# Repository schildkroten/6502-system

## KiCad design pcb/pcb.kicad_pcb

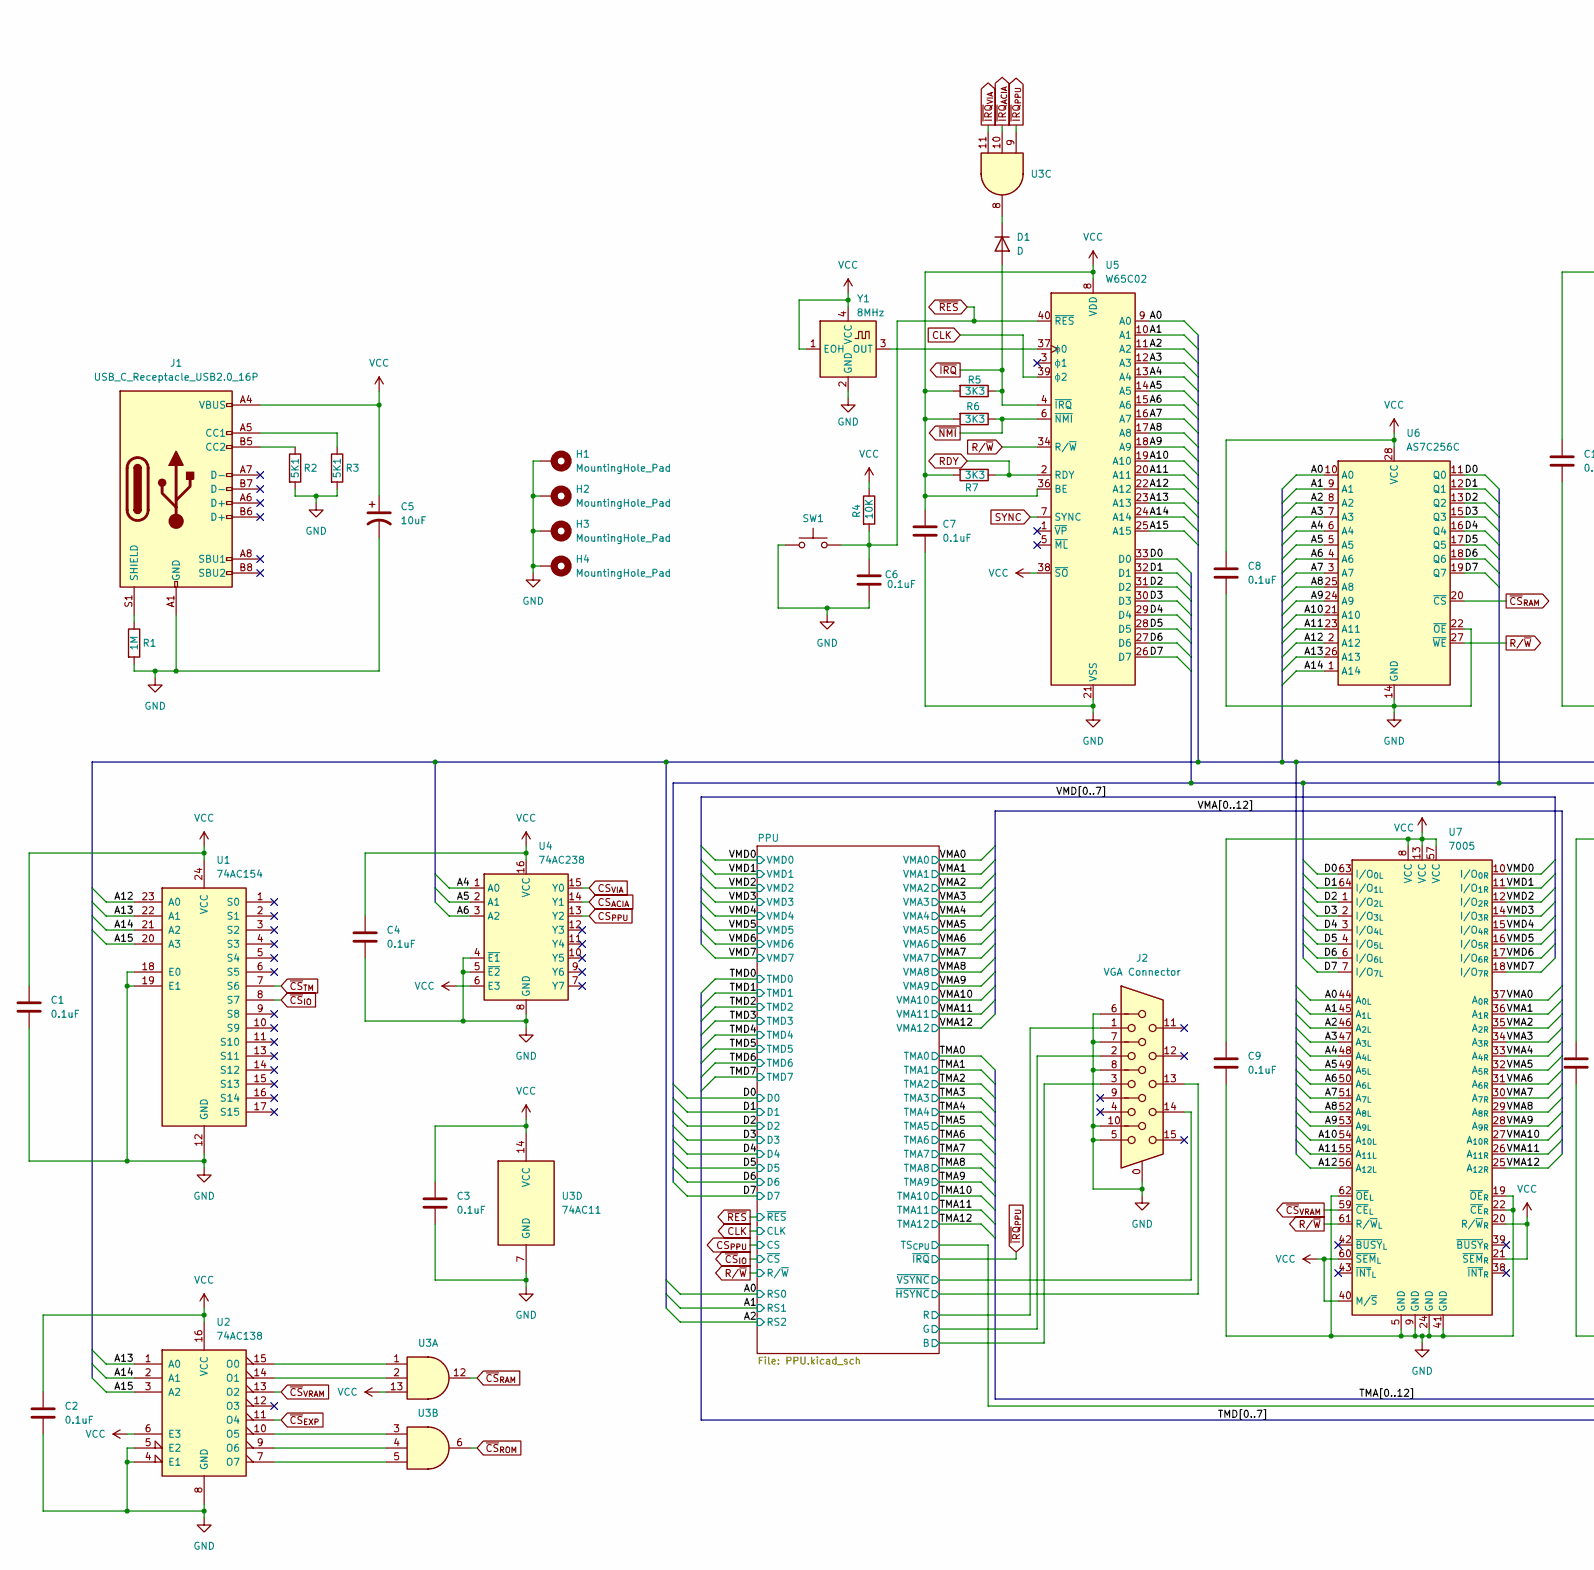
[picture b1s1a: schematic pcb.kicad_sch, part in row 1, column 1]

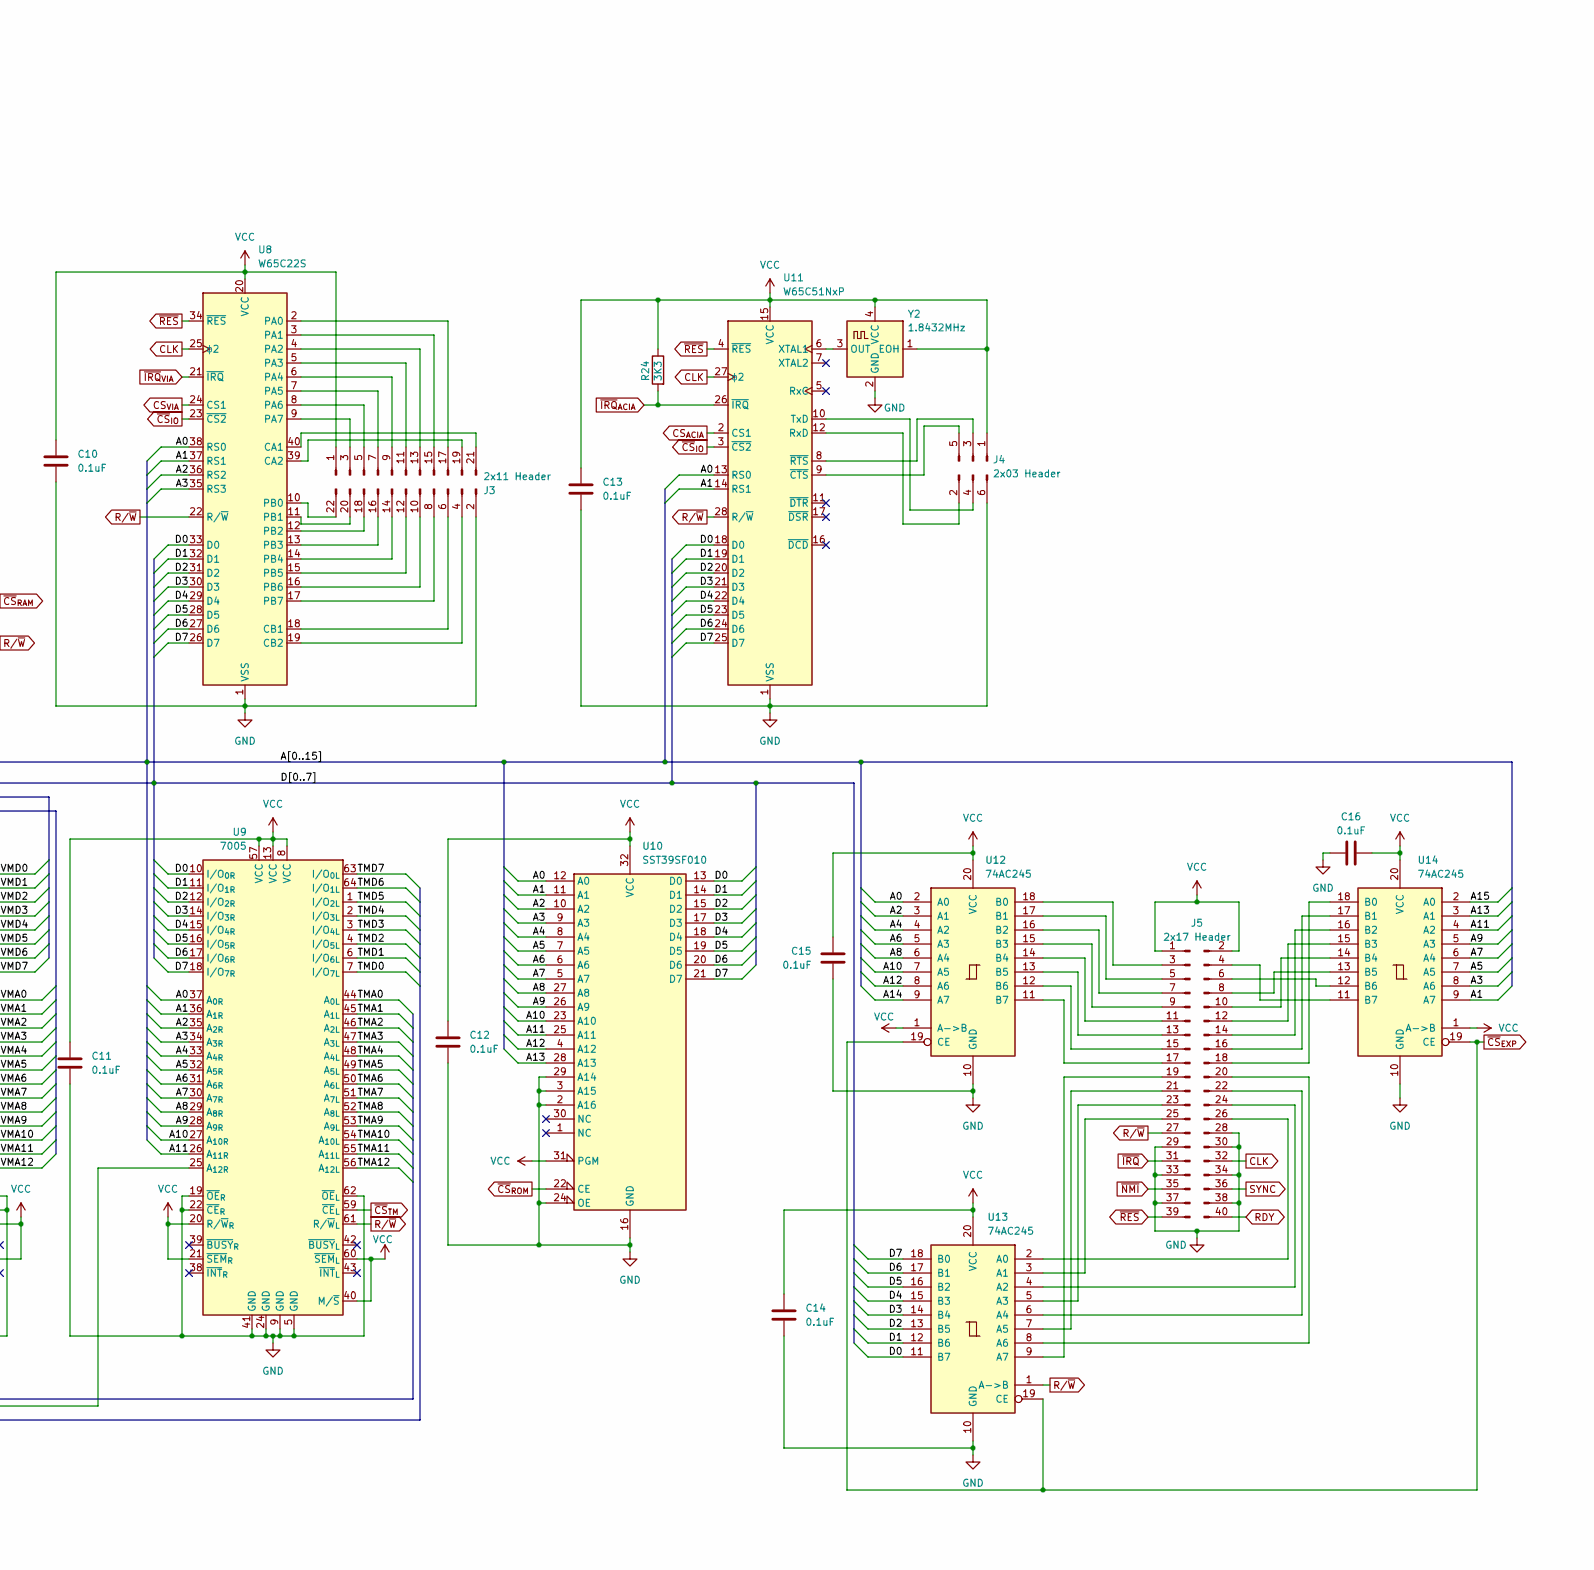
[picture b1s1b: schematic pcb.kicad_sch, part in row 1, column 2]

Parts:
C1, C2, C3, C4, C6, C7, C8, C9, C10, C11, C12, C13, C14, C15, C16: 0.1uF; C_0805_2012Metric
C5: 10uF; C_Radial_D5.0mm_H7.0mm_P2.00mm
D1: D
H1, H2, H3, H4: MountingHole_Pad; MountingHole_3.2mm_M3_Pad
J1: USB_C_Receptacle_USB2.0_16P; USB_C_Receptacle_GCT_USB4085
J2: VGA Connector; DSUB-15-HD_Socket_Horizontal_P2.29x2.54mm_EdgePinOffset8.35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
J3: 2x11 Header; IDC-Header_2x11_P2.54mm_Horizontal
J4: 2x03 Header; IDC-Header_2x03_P2.54mm_Horizontal
J5: 2x17 Header; IDC-Header_2x20_P2.54mm_Horizontal
R1: 1M; R_0805_2012Metric
R2, R3: 5K1; R_0805_2012Metric
R4: 10K; R_0805_2012Metric
R5, R6, R7, R24: 3K3; R_0805_2012Metric
SW1: SW_Push; SW_PUSH_6mm
U1: 74AC154; SOIC-24W_7.5x15.4mm_P1.27mm
U2: 74AC138; SOIC-16_3.9x9.9mm_P1.27mm
U3: 74AC11; SOIC-14_3.9x8.7mm_P1.27mm
U4: 74AC238; SOIC-16_3.9x9.9mm_P1.27mm
U5: W65C02; DIP-40_W15.24mm_Socket
U6: AS7C256C; DIP-28_W7.62mm_Socket
U7, U9: 7005; TQFP-64_14x14mm_P0.8mm
U8: W65C22S; DIP-40_W15.24mm_Socket
U10: SST39SF010; PLCC-32_THT-Socket
U11: W65C51NxP; DIP-28_W15.24mm_Socket
U12, U13, U14: 74AC245; TSSOP-20_4.4x6.5mm_P0.65mm
Y1: 8MHz; Oscillator_SMD_SeikoEpson_SG8002CA-4Pin_7.0x5.0mm
Y2: 1.8432MHz; Oscillator_SMD_SeikoEpson_SG8002CA-4Pin_7.0x5.0mm

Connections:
/A0: U5.9 (A0), U6.10 (A0), U7.44 (A_{0L}), U8.38 (RS0), U9.37 (A_{0R}), U10.12 (A0), U11.13 (RS0), U12.2 (A0); also elsewhere on the board
/A1: U5.10 (A1), U6.9 (A1), U7.45 (A_{1L}), U8.37 (RS1), U9.36 (A_{1R}), U10.11 (A1), U11.14 (RS1), U14.9 (A7); also elsewhere on the board
/A2: U5.11 (A2), U6.8 (A2), U7.46 (A_{2L}), U8.36 (RS2), U9.35 (A_{2R}), U10.10 (A2), U12.3 (A1); also elsewhere on the board
/A3: U5.12 (A3), U6.7 (A3), U7.47 (A_{3L}), U8.35 (RS3), U9.34 (A_{3R}), U10.9 (A3), U14.8 (A6)
/A4: U4.1 (A0), U5.13 (A4), U6.6 (A4), U7.48 (A_{4L}), U9.33 (A_{4R}), U10.8 (A4), U12.4 (A2)
/A5: U4.2 (A1), U5.14 (A5), U6.5 (A5), U7.49 (A_{5L}), U9.32 (A_{5R}), U10.7 (A5), U14.7 (A5)
/A6: U4.3 (A2), U5.15 (A6), U6.4 (A6), U7.50 (A_{6L}), U9.31 (A_{6R}), U10.6 (A6), U12.5 (A3)
/A7: U5.16 (A7), U6.3 (A7), U7.51 (A_{7L}), U9.30 (A_{7R}), U10.5 (A7), U14.6 (A4)
/A8: U5.17 (A8), U6.25 (A8), U7.52 (A_{8L}), U9.29 (A_{8R}), U10.27 (A8), U12.6 (A4)
/A9: U5.18 (A9), U6.24 (A9), U7.53 (A_{9L}), U9.28 (A_{9R}), U10.26 (A9), U14.5 (A3)
/A10: U5.19 (A10), U6.21 (A10), U7.54 (A_{10L}), U9.27 (A_{10R}), U10.23 (A10), U12.7 (A5)
/A11: U5.20 (A11), U6.23 (A11), U7.55 (A_{11L}), U9.26 (A_{11R}), U10.25 (A11), U14.4 (A2)
/A12: U1.23 (A0), U5.22 (A12), U6.2 (A12), U7.56 (A_{12L}), U10.4 (A12), U12.8 (A6)
/A13: U1.22 (A1), U2.1 (A0), U5.23 (A13), U6.26 (A13), U10.28 (A13), U14.3 (A1)
/A14: U1.21 (A2), U2.2 (A1), U5.24 (A14), U6.1 (A14), U12.9 (A7)
/A15: U1.20 (A3), U2.3 (A2), U5.25 (A15), U14.2 (A0)
/D0: U5.33 (D0), U6.11 (Q0), U7.63 (I/O_{0L}), U8.33 (D0), U9.10 (I/O_{0R}), U10.13 (D0), U11.18 (D0), U13.11 (B7); also elsewhere on the board
/D1: U5.32 (D1), U6.12 (Q1), U7.64 (I/O_{1L}), U8.32 (D1), U9.11 (I/O_{1R}), U10.14 (D1), U11.19 (D1), U13.12 (B6); also elsewhere on the board
/D2: U5.31 (D2), U6.13 (Q2), U7.1 (I/O_{2L}), U8.31 (D2), U9.12 (I/O_{2R}), U10.15 (D2), U11.20 (D2), U13.13 (B5); also elsewhere on the board
/D3: U5.30 (D3), U6.15 (Q3), U7.2 (I/O_{3L}), U8.30 (D3), U9.14 (I/O_{3R}), U10.17 (D3), U11.21 (D3), U13.14 (B4); also elsewhere on the board
/D4: U5.29 (D4), U6.16 (Q4), U7.3 (I/O_{4L}), U8.29 (D4), U9.15 (I/O_{4R}), U10.18 (D4), U11.22 (D4), U13.15 (B3); also elsewhere on the board
/D5: U5.28 (D5), U6.17 (Q5), U7.4 (I/O_{5L}), U8.28 (D5), U9.16 (I/O_{5R}), U10.19 (D5), U11.23 (D5), U13.16 (B2); also elsewhere on the board
/D6: U5.27 (D6), U6.18 (Q6), U7.6 (I/O_{6L}), U8.27 (D6), U9.17 (I/O_{6R}), U10.20 (D6), U11.24 (D6), U13.17 (B1); also elsewhere on the board
/D7: U5.26 (D7), U6.19 (Q7), U7.7 (I/O_{7L}), U8.26 (D7), U9.18 (I/O_{7R}), U10.21 (D7), U11.25 (D7), U13.18 (B0); also elsewhere on the board
/PPU/B: J2.3; also elsewhere on the board
/PPU/G: J2.2; also elsewhere on the board
/PPU/R: J2.1; also elsewhere on the board
/PPU/TS_{CPU}: U9.25 (A_{12R}); also elsewhere on the board
/PPU/~HSYNC: J2.13; also elsewhere on the board
/PPU/~VSYNC: J2.14; also elsewhere on the board
/TMA0: U9.44 (A_{0L}); also elsewhere on the board
/TMA1: U9.45 (A_{1L}); also elsewhere on the board
/TMA2: U9.46 (A_{2L}); also elsewhere on the board
/TMA3: U9.47 (A_{3L}); also elsewhere on the board
/TMA4: U9.48 (A_{4L}); also elsewhere on the board
/TMA5: U9.49 (A_{5L}); also elsewhere on the board
/TMA6: U9.50 (A_{6L}); also elsewhere on the board
/TMA7: U9.51 (A_{7L}); also elsewhere on the board
/TMA8: U9.52 (A_{8L}); also elsewhere on the board
/TMA9: U9.53 (A_{9L}); also elsewhere on the board
/TMA10: U9.54 (A_{10L}); also elsewhere on the board
/TMA11: U9.55 (A_{11L}); also elsewhere on the board
/TMA12: U9.56 (A_{12L}); also elsewhere on the board
/TMD0: U9.7 (I/O_{7L}); also elsewhere on the board
/TMD1: U9.6 (I/O_{6L}); also elsewhere on the board
/TMD2: U9.4 (I/O_{5L}); also elsewhere on the board
/TMD3: U9.3 (I/O_{4L}); also elsewhere on the board
/TMD4: U9.2 (I/O_{3L}); also elsewhere on the board
/TMD5: U9.1 (I/O_{2L}); also elsewhere on the board
/TMD6: U9.64 (I/O_{1L}); also elsewhere on the board
/TMD7: U9.63 (I/O_{0L}); also elsewhere on the board
/VMA0: U7.37 (A_{0R}); also elsewhere on the board
/VMA1: U7.36 (A_{1R}); also elsewhere on the board
/VMA2: U7.35 (A_{2R}); also elsewhere on the board
/VMA3: U7.34 (A_{3R}); also elsewhere on the board
/VMA4: U7.33 (A_{4R}); also elsewhere on the board
/VMA5: U7.32 (A_{5R}); also elsewhere on the board
/VMA6: U7.31 (A_{6R}); also elsewhere on the board
/VMA7: U7.30 (A_{7R}); also elsewhere on the board
/VMA8: U7.29 (A_{8R}); also elsewhere on the board
/VMA9: U7.28 (A_{9R}); also elsewhere on the board
/VMA10: U7.27 (A_{10R}); also elsewhere on the board
/VMA11: U7.26 (A_{11R}); also elsewhere on the board
/VMA12: U7.25 (A_{12R}); also elsewhere on the board
/VMD0: U7.10 (I/O_{0R}); also elsewhere on the board
/VMD1: U7.11 (I/O_{1R}); also elsewhere on the board
/VMD2: U7.12 (I/O_{2R}); also elsewhere on the board
/VMD3: U7.14 (I/O_{3R}); also elsewhere on the board
/VMD4: U7.15 (I/O_{4R}); also elsewhere on the board
/VMD5: U7.16 (I/O_{5R}); also elsewhere on the board
/VMD6: U7.17 (I/O_{6R}); also elsewhere on the board
/VMD7: U7.18 (I/O_{7R}); also elsewhere on the board
CLK: J5.32, U5.39 (ϕ2), U8.25 (ϕ2), U11.27 (ϕ2); also elsewhere on the board
CS_{ACIA}: U4.14 (Y1), U11.2 (CS1)
CS_{PPU}: U4.13 (Y2); also elsewhere on the board
CS_{VIA}: U4.15 (Y0), U8.24 (CS1)
GND: C1.2, C2.2, C3.2, C4.2, C5.2, C6.1, C7.2, C8.2, C9.2, C10.2, C11.2, C12.2, C13.2, C14.2, C15.2, C16.1, H1.1, H2.1, H3.1, H4.1, J1.A1 (GND), J1.A12 (GND), J1.B1 (GND), J1.B12 (GND), J2.0, J2.5, J2.6, J2.7, J2.8, J2.10, J3.2, J4.6, J5.28, J5.29, J5.30, J5.33, J5.34, J5.37, J5.38, R1.2, R2.2, R3.2, SW1.1, U1.12 (GND), U1.18 (E0), U1.19 (E1), U2.4 (E1), U2.5 (E2), U2.8 (GND), U3.7 (GND), U4.4 (~E1), U4.5 (~E2), U4.8 (GND), U5.21 (VSS), U6.14 (GND), U6.22 (~OE), U7.5 (GND), U7.9 (GND), U7.19 (~OE_{R}), U7.22 (~CE_{R}), U7.24 (GND), U7.41 (GND), U7.62 (~OE_{L}), U8.1 (VSS), U9.5 (GND), U9.9 (GND), U9.19 (~OE_{R}), U9.22 (~CE_{R}), U9.24 (GND), U9.41 (GND), U9.62 (~OE_{L}), U10.2 (A16), U10.3 (A15), U10.16 (GND), U10.24 (OE), U10.29 (A14), U11.1 (VSS), U12.10 (GND), U13.10 (GND), U14.10 (GND), Y1.2 (GND), Y2.2 (GND); also elsewhere on the board
unnamed: D1.1 (K), U3.8
unnamed: J1.A5 (CC1), R3.1
unnamed: J1.B5 (CC2), R2.1
unnamed: J1.S1 (SHIELD), R1.1
unnamed: U2.15 (O0), U3.1
unnamed: U2.14 (O1), U3.2
unnamed: U2.10 (O5), U3.3
unnamed: U2.9 (O6), U3.4
unnamed: U2.7 (O7), U3.5
unnamed: U5.37 (ϕ0), Y1.3 (OUT)
unnamed: J3.21, U8.40 (CA1)
unnamed: J3.19, U8.39 (CA2)
unnamed: J3.6, U8.18 (CB1)
unnamed: J3.4, U8.19 (CB2)
unnamed: J3.17, U8.2 (PA0)
unnamed: J3.15, U8.3 (PA1)
unnamed: J3.13, U8.4 (PA2)
unnamed: J3.11, U8.5 (PA3)
unnamed: J3.9, U8.6 (PA4)
unnamed: J3.7, U8.7 (PA5)
unnamed: J3.5, U8.8 (PA6)
unnamed: J3.3, U8.9 (PA7)
unnamed: J3.22, U8.10 (PB0)
unnamed: J3.20, U8.11 (PB1)
unnamed: J3.18, U8.12 (PB2)
unnamed: J3.16, U8.13 (PB3)
unnamed: J3.14, U8.14 (PB4)
unnamed: J3.12, U8.15 (PB5)
unnamed: J3.10, U8.16 (PB6)
unnamed: J3.8, U8.17 (PB7)
unnamed: J4.2, U11.12 (RxD)
unnamed: J4.4, U11.10 (TxD)
unnamed: U11.6 (XTAL1), Y2.3 (OUT)
unnamed: J4.5, U11.9 (~CTS)
unnamed: J4.3, U11.8 (~RTS)
unnamed: J5.3, U12.18 (B0)
unnamed: J5.5, U12.17 (B1)
unnamed: J5.7, U12.16 (B2)
unnamed: J5.9, U12.15 (B3)
unnamed: J5.11, U12.14 (B4)
unnamed: J5.13, U12.13 (B5)
unnamed: J5.15, U12.12 (B6)
unnamed: J5.17, U12.11 (B7)
unnamed: J5.26, U13.2 (A0)
unnamed: J5.25, U13.3 (A1)
unnamed: J5.24, U13.4 (A2)
unnamed: J5.23, U13.5 (A3)
unnamed: J5.22, U13.6 (A4)
unnamed: J5.21, U13.7 (A5)
unnamed: J5.20, U13.8 (A6)
unnamed: J5.19, U13.9 (A7)
unnamed: J5.18, U14.18 (B0)
unnamed: J5.16, U14.17 (B1)
unnamed: J5.14, U14.16 (B2)
unnamed: J5.12, U14.15 (B3)
unnamed: J5.10, U14.14 (B4)
unnamed: J5.8, U14.13 (B5)
unnamed: J5.6, U14.12 (B6)
unnamed: J5.4, U14.11 (B7)
RDY: J5.40, R7.1, U5.2 (RDY)
R/~W: J5.27, U5.34 (R/~W), U6.27 (~WE), U7.61 (R/~W_{L}), U8.22 (R/~W), U9.61 (R/~W_{L}), U11.28 (R/~W), U13.1 (A->B); also elsewhere on the board
SYNC: J5.36, U5.7 (SYNC)
VCC: C1.1, C2.1, C3.1, C4.1, C5.1, C7.1, C8.1, C9.1, C10.1, C11.1, C12.1, C13.1, C14.1, C15.1, C16.2, J1.A4 (VBUS), J1.A9 (VBUS), J1.B4 (VBUS), J1.B9 (VBUS), J3.1, J4.1, J5.1, J5.2, R4.1, R5.2, R6.2, R7.2, R24.1, U1.24 (VCC), U2.6 (E3), U2.16 (VCC), U3.13, U3.14 (VCC), U4.6 (E3), U4.16 (VCC), U5.8 (VDD), U5.36 (BE), U5.38 (~SO), U6.28 (VCC), U7.8 (VCC), U7.13 (VCC), U7.20 (R/~W_{R}), U7.21 (~SEM_{R}), U7.40 (M/~S), U7.57 (VCC), U7.60 (~SEM_{L}), U8.20 (VCC), U9.8 (VCC), U9.13 (VCC), U9.20 (R/~W_{R}), U9.21 (~SEM_{R}), U9.40 (M/~S), U9.57 (VCC), U9.60 (~SEM_{L}), U10.31 (PGM), U10.32 (VCC), U11.15 (VCC), U12.1 (A->B), U12.20 (VCC), U13.20 (VCC), U14.1 (A->B), U14.20 (VCC), Y1.1 (EOH), Y1.4 (VCC), Y2.1 (EOH), Y2.4 (VCC); also elsewhere on the board
~CS_{EXP}: U2.11 (O4), U12.19 (CE), U13.19 (CE), U14.19 (CE)
~CS_{IO}: U1.8 (S7), U8.23 (~CS2), U11.3 (~CS2); also elsewhere on the board
~CS_{RAM}: U3.12, U6.20 (~CS)
~CS_{ROM}: U3.6, U10.22 (CE)
~CS_{TM}: U1.7 (S6), U9.59 (~CE_{L})
~CS_{VRAM}: U2.13 (O2), U7.59 (~CE_{L})
~IRQ: D1.2 (A), J5.31, R5.1, U5.4 (~IRQ)
~IRQ_{ACIA}: R24.2, U3.10, U11.26 (~IRQ)
~IRQ_{PPU}: U3.9; also elsewhere on the board
~IRQ_{VIA}: U3.11, U8.21 (~IRQ)
~NMI: J5.35, R6.1, U5.6 (~NMI)
~RES: C6.2, J5.39, R4.2, SW1.2, U5.40 (~RES), U8.34 (~RES), U11.4 (~RES); also elsewhere on the board
